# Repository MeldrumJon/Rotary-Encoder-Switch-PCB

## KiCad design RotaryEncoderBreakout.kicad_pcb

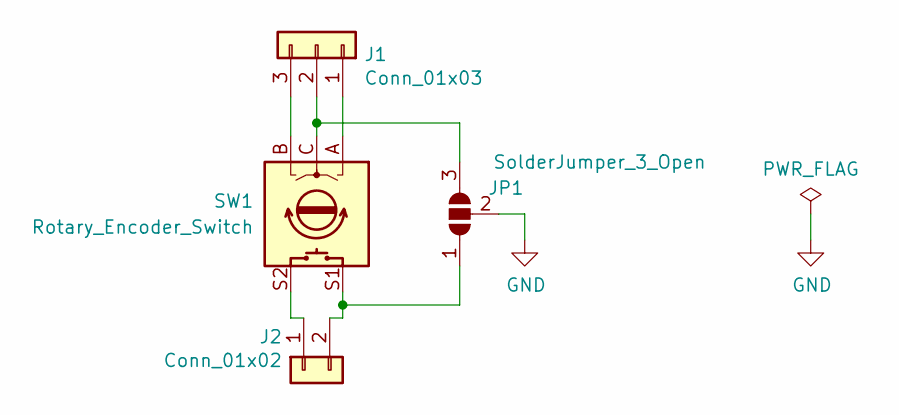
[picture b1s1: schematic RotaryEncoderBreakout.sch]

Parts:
J1: Conn_01x03; PinHeader_1x03_P2.54mm_Vertical
J2: Conn_01x02; PinHeader_1x02_P2.54mm_Vertical
JP1: SolderJumper_3_Open; SolderJumper-3_P1.3mm_Open_Pad1.0x1.5mm
SW1: Rotary_Encoder_Switch; RotaryEncoder_Alps_EC12E-Switch_Vertical_H20mm

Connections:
GND: JP1.2 (C)
unnamed: J1.1, SW1.A
unnamed: J1.2, JP1.3 (B), SW1.C
unnamed: J1.3, SW1.B
unnamed: J2.1, SW1.S2
unnamed: J2.2, JP1.1 (A), SW1.S1

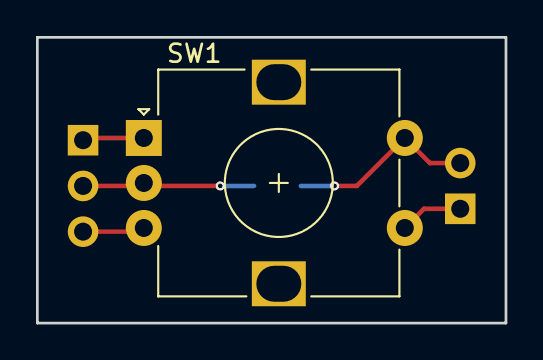
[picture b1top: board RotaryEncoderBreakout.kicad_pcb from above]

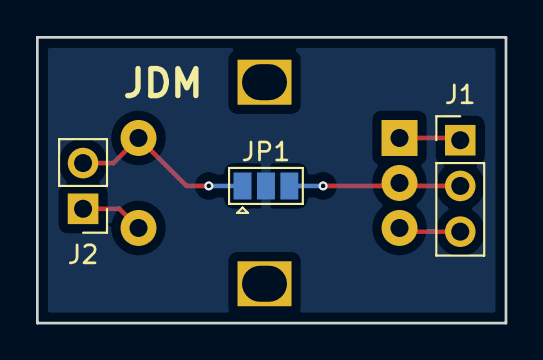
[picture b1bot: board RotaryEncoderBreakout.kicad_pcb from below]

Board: 2 copper layers, 26.0 x 15.9 mm, 4 parts (3 on the bottom side), 5 nets.

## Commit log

2019-09-11 PCB v0.1
2019-09-13 Added images
